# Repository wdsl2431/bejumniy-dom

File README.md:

# bejumniy-dom
каждый, вошедший сюда, должен положить рубль себе под язык и выйти

Что то похожее на правду про двины
https://www.youtube.com/watch?v=0M20iCJkjQU

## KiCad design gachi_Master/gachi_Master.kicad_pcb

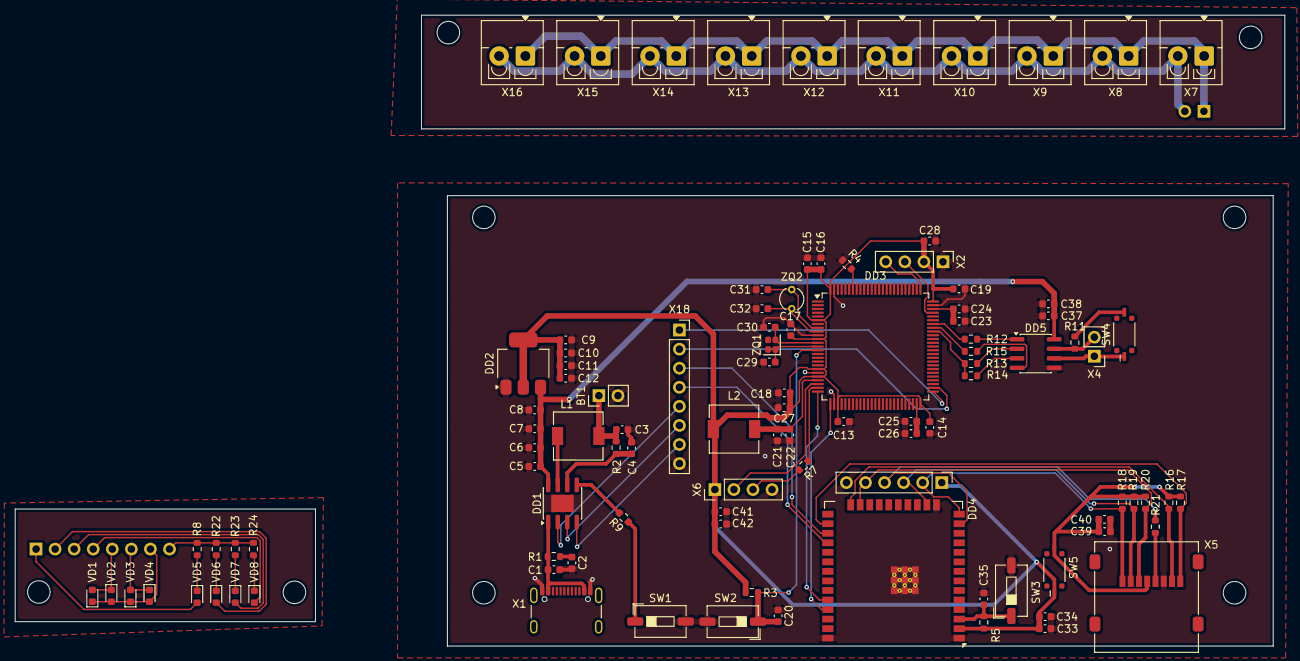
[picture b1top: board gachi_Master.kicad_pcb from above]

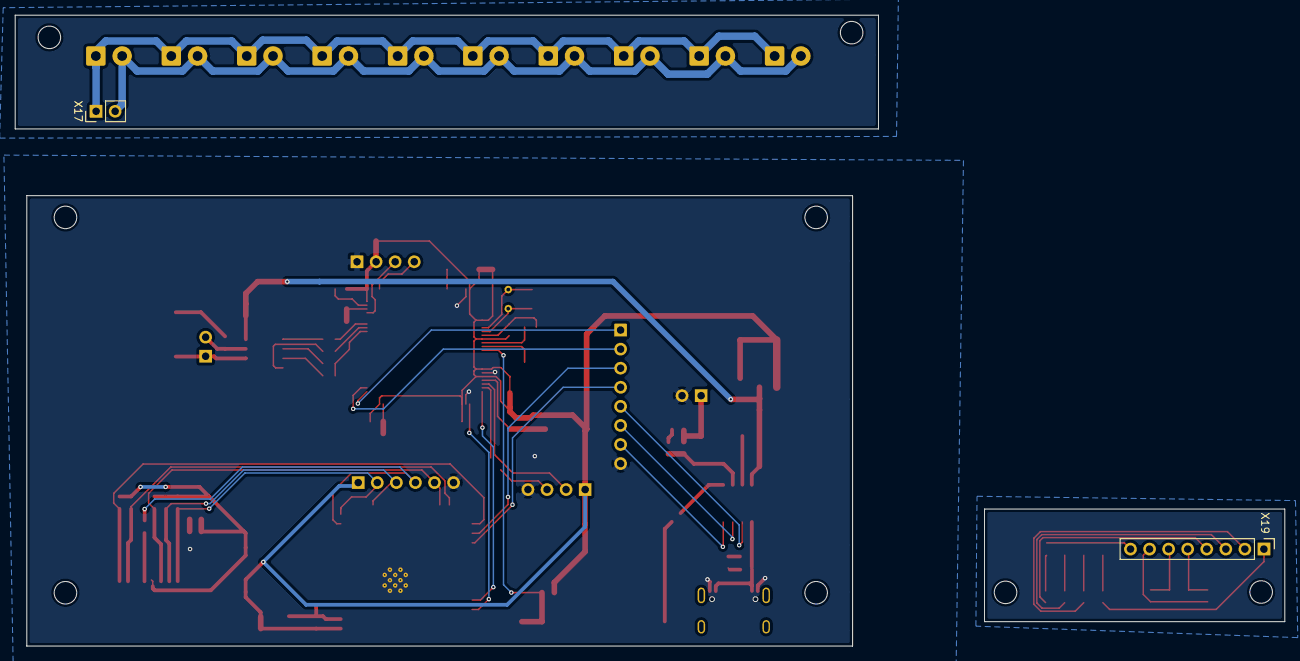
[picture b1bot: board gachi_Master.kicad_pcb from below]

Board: 2 copper layers, 169.1 x 84.0 mm, 105 parts (2 on the bottom side), 66 nets.

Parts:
BT1: Li-ion; PinHeader_1x02_P2.54mm_Vertical
C1, C2: 10мкФ; C_0603_1608Metric
C3, C4, C5, C6, C7, C8, C9, C10: 22мкФ; C_0603_1608Metric
C11, C12, C13, C14, C15, C16, C17, C18, C19, C20, C21, C23, C25, C27, C28, C34, C35, C38, C39, C41: 0,1мкФ; C_0603_1608Metric
C22, C33, C37, C40, C42: 1мкФ; C_0603_1608Metric
C24, C26: 2,2мкФ; C_0603_1608Metric
C29, C30: 18пФ; C_0603_1608Metric
C31: 10пФ; C_0603_1608Metric
C32: 10Ф; C_0603_1608Metric
DD1: IP5306; SOIC-8-1EP_3.9x4.9mm_P1.27mm_EP2.29x3mm
DD2: AMS1117-3.3; SOT-223-3_TabPin2
DD3: STM32F407VGTx; LQFP-100_14x14mm_P0.5mm
DD4: ESP32-WROOM-32E
DD5: MAX485E; SOIC-8_3.9x4.9mm_P1.27mm
L1: 1 мкГн; L_6.3x6.3_H3
L2: 10мкГн; L_6.3x6.3_H3
R1: 2; R_0603_1608Metric
R2: 0.5; R_0603_1608Metric
R3, R4, R5, R9, R12, R13, R14, R15, R16, R17, R18, R19, R20: 10k; R_0603_1608Metric
R7, R8, R22, R23, R24: 300; R_0603_1608Metric
R11: 120; R_0603_1608Metric
R21: 33; R_0603_1608Metric
SW1, SW2, SW3: SW_Push; SW_DIP_SPSTx01_Slide_6.7x4.1mm_W6.73mm_P2.54mm_LowProfile_J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
SW4, SW5: SW_SPDT; SW_DIP_SPSTx01_Slide_Copal_CVS-01xB_W5.9mm_P1mm
VD1, VD2, VD3, VD4, VD5, VD6, VD7, VD8: LED; LED_0603_1608Metric
X1: USB_C_Receptacle_USB2.0_16P; USB_C_Receptacle_GCT_USB4105-xx-A_16P_TopMnt_Horizontal
X2: Conn_01x04; PinHeader_1x04_P2.54mm_Vertical
X3: Conn_01x06_Pin; PinHeader_1x06_P2.54mm_Vertical
X4, X17: Conn_01x02_Pin; PinHeader_1x02_P2.54mm_Vertical
X5: Micro_SD_Card; microSD_HC_Molex_47219-2001
X6: Conn_01x04_Pin; PinHeader_1x04_P2.54mm_Vertical
X7, X8, X9, X10, X11, X12, X13, X14, X15, X16: Screw_Terminal_01x02; TerminalBlock_4Ucon_1x02_P3.50mm_Vertical
X18: Conn_01x08_Socket; PinSocket_1x08_P2.54mm_Vertical
X19: Conn_01x08_Pin; PinHeader_1x08_P2.54mm_Vertical
ZQ1: WTL5M85611FO; Crystal_SMD_WE_IQXC-42-4Pin_2.0x1.6mm
ZQ2: 32.768; Crystal_AT310_D3.0mm_L10.0mm_Vertical

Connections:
3,3 В: C9.1, C10.1, C11.1, C12.1, C13.1, C14.1, C15.1, C16.1, C17.1, C18.1, C19.1, C27.1, C28.1, C33.1, C34.1, C41.1, C42.1, DD2.2 (VO), DD3.6 (VBAT), DD3.11 (VDD), DD3.19 (VDD), DD3.21 (VREF+), DD3.28 (VDD), DD3.50 (VDD), DD3.75 (VDD), DD3.100 (VDD), DD4.2 (VDD), L2.1, R3.1, R5.2, SW5.1 (A), X2.2, X3.1, X6.1
5 В: C5.1, C6.1, C7.1, C8.1, C37.1, C38.1, DD1.8 (VOUT), DD2.3 (VI), DD5.8 (VCC)
DWIN_RX: R7.2, X6.3
DWIN_TX: DD3.23 (PA0), X6.2
ESP_LED_ERROR: DD4.28 (IO17), X18.4
ESP_LED_STATE: DD4.27 (IO16), X18.3
ESP_RX: DD3.26 (PA3), DD4.35 (TXD0/IO1)
ESP_TX: DD3.25 (PA2), DD4.34 (RXD0/IO3)
GND: BT1.2 (-), C1.2, C2.2, C3.2, C4.2, C5.2, C6.2, C7.2, C8.2, C9.2, C10.2, C11.2, C12.2, C13.2, C14.2, C15.2, C16.2, C17.2, C18.2, C19.2, C20.1, C21.2, C22.2, C23.2, C24.2, C25.2, C26.2, C27.2, C28.2, C29.2, C30.2, C31.2, C32.2, C33.2, C34.2, C35.2, C37.2, C38.2, C39.2, C40.2, C41.2, C42.2, DD1.9 (GND), DD2.1 (GND), DD3.10 (VSS), DD3.20 (VSSA), DD3.27 (VSS), DD3.74 (VSS), DD3.99 (VSS), DD4.1 (GND), DD4.15 (GND), DD4.38 (GND), DD4.39 (GND), DD5.5 (GND), R4.1, SW1.2, SW2.2, SW3.2, X1.A1 (GND), X1.A12 (GND), X1.B1 (GND), X1.B12 (GND), X2.1, X3.6, X5.6 (VSS), X6.4, X18.8
IP_LED_1: DD1.2 (LED1), X18.5
IP_LED_2: DD1.3 (LED2), X18.6
IP_LED_3: DD1.4 (LED3), X18.7
unnamed: BT1.1 (+), C3.1, L1.2, R2.1
unnamed: C2.1, R1.2
unnamed: C4.1, DD1.6 (BAT), R2.2
unnamed: DD1.5 (KEY), R9.2
unnamed: DD1.7 (SW), L1.1
unnamed: C1.1, DD1.1 (VIN), R1.1, X1.A4 (VBUS), X1.A9 (VBUS), X1.B4 (VBUS), X1.B9 (VBUS)
unnamed: DD3.94 (BOOT0), R4.2
unnamed: C20.2, DD3.14 (NRST), R3.2, SW2.1
unnamed: DD3.24 (PA1), R7.1
unnamed: DD3.72 (PA13), X2.3
unnamed: DD3.76 (PA14), X2.4
unnamed: C25.1, C26.1, DD3.49 (VCAP_1)
unnamed: C23.1, C24.1, DD3.73 (VCAP_2)
unnamed: C21.1, C22.1, DD3.22 (VDDA), L2.2
unnamed: C35.1, DD4.3 (EN), R5.1, SW3.1
unnamed: DD5.6 (A), SW4.1 (A), X4.1
unnamed: DD5.7 (B), R11.2, X4.2
unnamed: DD5.3 (DE), R14.1
unnamed: DD5.4 (DI), R15.1
unnamed: DD5.1 (RO), R12.1
unnamed: DD5.2 (~RE), R13.1
unnamed: R9.1, SW1.1
unnamed: R11.1, SW4.2 (B)
unnamed: C39.1, C40.1, R16.2, R17.2, R18.2, R19.2, R20.2, SW5.2 (B), X5.4 (VDD)
unnamed: VD1.2 (A), VD2.1 (K), X19.5
unnamed: VD1.1 (K), VD2.2 (A), VD3.1 (K), VD4.2 (A), X19.7
unnamed: VD3.2 (A), VD4.1 (K), X19.6
unnamed: VD5.2 (A), X19.1
unnamed: R8.1, VD5.1 (K)
unnamed: VD6.2 (A), X19.2
unnamed: R22.1, VD6.1 (K)
unnamed: VD7.2 (A), X19.3
unnamed: R23.1, VD7.1 (K)
unnamed: VD8.2 (A), X19.4
unnamed: R24.1, VD8.1 (K)
unnamed: R21.1, X5.5 (CLK)
unnamed: X7.1, X8.1, X9.1, X10.1, X11.1, X12.1, X13.1, X14.1, X15.1, X16.1, X17.1
unnamed: X7.2, X8.2, X9.2, X10.2, X11.2, X12.2, X13.2, X14.2, X15.2, X16.2, X17.2
unnamed: R8.2, R22.2, R23.2, R24.2, X19.8
OSC_IN_HSE: C30.1, DD3.12 (PH0), ZQ1.2
OSC_IN_LSE: C31.1, DD3.8 (PC14), ZQ2.2
OSC_OUT_HSE: C29.1, DD3.13 (PH1), ZQ1.1
OSC_OUT_LSE: C32.1, DD3.9 (PC15), ZQ2.1
RS485_RTS: DD3.67 (PA8), R13.2, R14.2
RS485_RX: DD3.69 (PA10), R12.2
RS485_TX: DD3.68 (PA9), R15.2
SD_CLK: DD4.13 (IO14), R21.2, X3.4
SD_CMD: DD4.23 (IO15), R20.1, X3.5, X5.3 (CMD)
SD_DAT0: DD4.24 (IO2), R16.1, X5.7 (DAT0)
SD_DAT1: DD4.26 (IO4), R17.1, X5.8 (DAT1)
SD_DAT2: DD4.14 (IO12), R18.1, X3.2, X5.1 (DAT2)
SD_DAT3/CD: DD4.16 (IO13), R19.1, X3.3, X5.2 (DAT3/CD)
STM_LED_ERROR: DD3.52 (PB13), X18.2
STM_LED_STATE: DD3.51 (PB12), X18.1
